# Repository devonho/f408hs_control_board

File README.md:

# Control board for Panasonic F-408HS 16" Stand Fan

## *** Warning  ***

This repository contains circuit designs for a printed circuit board that uses 240VAC as a power source, and can hence cause serious injury or death to anyone who implements the design. 

## Disclaimer

By using any of the designs here, you agree to waive the author of all liability for any personal or 3rd party injury or death, or damage to property sustained as a result of using the designs.

## License

These designs were made using a free version of [Autodesk Eagle](http://eagle.autodesk.com). Commercial use of designs is prohibited.

Furthermore: [License](./LICENSE)

## Overview

The design contained here contains both a [schematic](./eagle/F408HS_control.sch) that is inspired by the original board design, and a board [layout](./eagle/F408HS_control.brd) that has been revamped and optimized for 2-layer fabrication and debugging.

## Components and BOM

Most of the components used have been listed in the [Bill-Of-Materials](./eagle/BOM.txt) list. Some special ones that were hard to locate are connectors for the motor (CN1) and the AC input to the control board itself. These are:

* Japan Automatic Machine (JAM) SC25-10WL
* Japan Solderless Terminals (JST) ELR-03V

### Component Values

Values for transistors Q1 and Q2 were determined based on SMD markings, which may be erroneous.

Values for capacitors and zener diode were determined empirically using simulation in [LTSpice](https://www.analog.com/en/design-center/design-tools-and-calculators/ltspice-simulator.html). 

## LT SPICE Simulations

* [Power](./spice/power.asc)
* [Phase Sync](./spice/phase_sync.asc)

## Layout

The [layout](./eagle/F408HS_control.brd) was designed with 2 layer boards in mind. Without the contraints of a single layer board, J1 - J3 are no longer needed to bridge over tracks.

The 240AC tracks have also been constrained to the right side of the board, making it slightly less risky while probing the board. The AC section can also be left unpopulated, using an externally sourced Vdd and Vss via CN2 for debugging the low voltage section. 

 ## Schematic

 ### AC Phase Sync

 The output of the AC phase sync circuit is connected to P13 of the MCU. Hence it is possible that the interrupt capability of that pin is used to synchronise the TRIAC trigger with the AC phase. Modulating the TRIAC duty cycle is probably needed for the 揺らぎ "Yuragi" fluctuation function, to lower the motor RPM.

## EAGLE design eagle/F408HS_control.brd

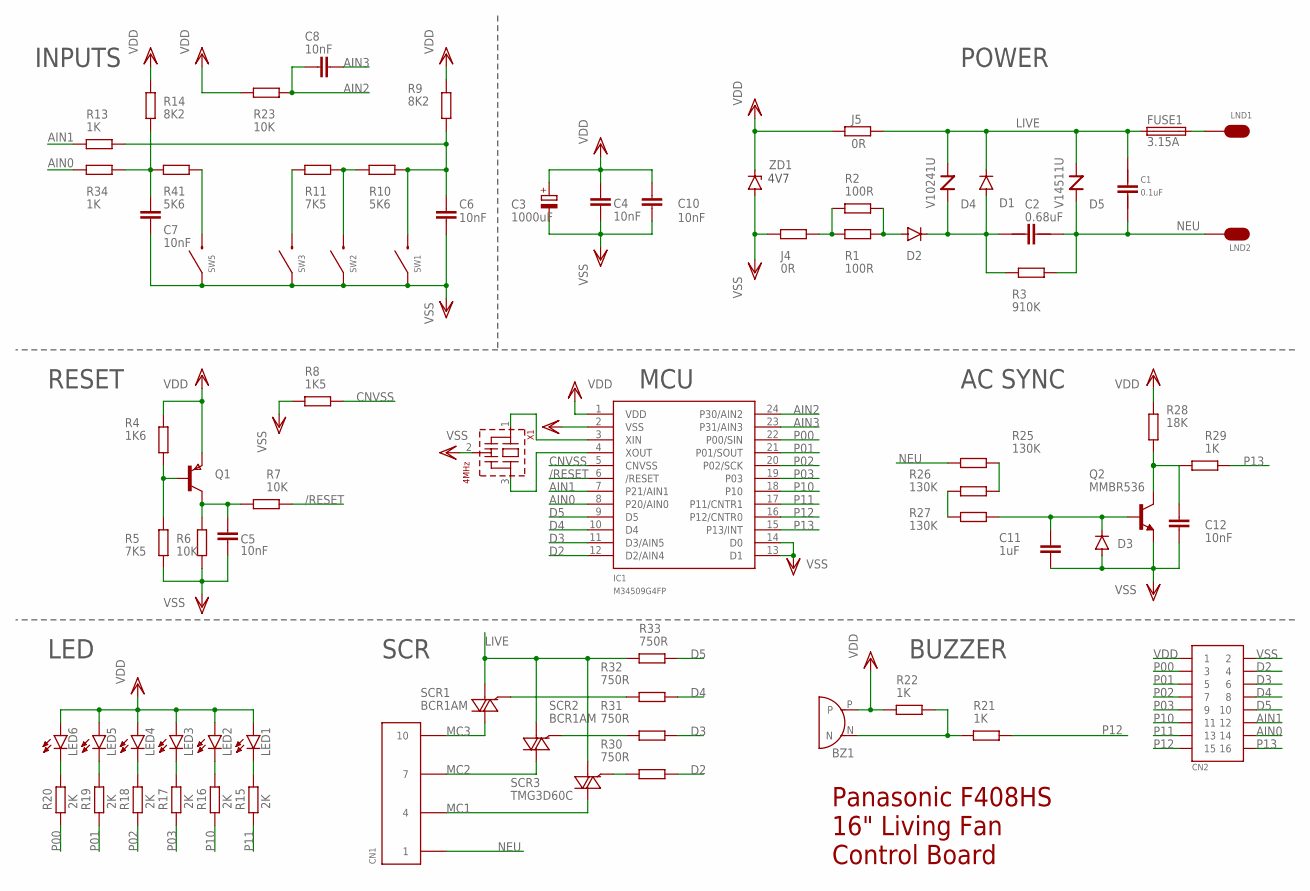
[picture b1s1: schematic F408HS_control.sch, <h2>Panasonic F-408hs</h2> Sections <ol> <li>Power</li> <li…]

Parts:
BZ1: BUZZER
C1: 0.1uF; ECQU2A104
C2: 0.68uF; ECQU2A684
C3: 1000uF; B45181B
C4, C5, C6, C7, C8, C10, C12: 10nF; C0805
C11: 1uF; C0805
CN1: SC25-10WS
CN2: HEADER16; PAK100/2500-16
D1, D2: SD103CWS-7-F; DO41-10
D3: DIODE-SOD106-W; SOD106-W
D4: V10241U; E14-S1
D5: V14511U; E14-S1
FUSE1: 3.15A; FUSE
IC1: M34509G4FP; SSOP24
J4, J5: 0R; M0805
LED1, LED2, LED3, LED4, LED5, LED6: LED_PTH_HORIZ; LED_HORIZ
LND1, LND2: LND
Q1: PNPSOT23; SOT-23
Q2: MMBR536; SOT23
R1, R2: 100R; 0204/7
R3: 910K; 0204/7
R4: 1K6; M0805
R5, R11: 7K5; M0805
R6, R7, R23: 10K; M0805
R8: 1K5; M0805
R9, R14: 8K2; M0805
R10, R41: 5K6; M0805
R13, R21, R22, R29, R34: 1K; M0805
R15, R16, R17, R18, R19, R20: 2K; M0805
R25, R26, R27: 130K; R0805
R28: 18K; M0805
R30, R31, R32, R33: 750R; M0805
SCR1, SCR2: BCR1AM; TO92
SCR3: TMG3D60C; TO220DS
SW1, SW2, SW3, SW5: EVQ11
X1: 4MHz; CSTLS_G8
ZD1: DDZ4V7ASF-7; DO35Z10

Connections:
/RESET: IC1.6 (/RESET), R7.1
AIN0: CN2.14, IC1.8 (P20/AIN0), R34.1
AIN1: CN2.12, IC1.7 (P21/AIN1), R13.1
AIN2: C8.1, IC1.24 (P30/AIN2), R23.1
AIN3: C8.2, IC1.23 (P31/AIN3)
CNVSS: IC1.5 (CNVSS), R8.1
D2: CN2.4, IC1.12 (D2/AIN4), R30.1
D3: CN2.6, IC1.11 (D3/AIN5), R31.1
D4: CN2.8, IC1.10 (D4), R32.1
D5: CN2.10, IC1.9 (D5), R33.1
LIVE: C1.P$1, D1.C, D4.P$1, D5.P$1, FUSE1.P$1 (1), J5.1, R33.2, SCR1.1 (A1), SCR2.1 (A1), SCR3.A1
MC1: CN1.P$4 (4), SCR3.A2
MC2: CN1.P$7 (7), SCR2.3 (A2)
MC3: CN1.P$10 (10), SCR1.3 (A2)
unnamed: R25.1, R26.2
unnamed: C12.2, Q2.3 (C), R28.2, R29.2
unnamed: R26.1, R27.2
unnamed: C2.P$1, D1.A, D2.C, D4.P$2, R3.1
unnamed: C6.2, R9.1, R10.2, R13.2, SW1.P$2
unnamed: C11.2, D3.C, Q2.1 (B), R27.1
unnamed: D2.A, R1.2, R2.2
unnamed: R30.2, SCR3.G
unnamed: Q1.3 (B), R4.1, R5.2
unnamed: C5.1, Q1.1 (C), R6.2, R7.2
unnamed: R10.1, R11.2, SW2.P$2
unnamed: R11.1, SW3.P$2
unnamed: R41.2, SW5.P$2
unnamed: C7.1, R14.1, R34.2, R41.1
unnamed: LED6.N (K), R20.2
unnamed: LED5.N (K), R19.2
unnamed: LED4.N (K), R18.2
unnamed: LED3.N (K), R17.2
unnamed: LED2.N (K), R16.2
unnamed: LED1.N (K), R15.2
unnamed: FUSE1.P$2 (2), LND1.P$1
unnamed: J4.1, R1.1, R2.1
unnamed: R32.2, SCR1.2 (G)
unnamed: R31.2, SCR2.2 (G)
unnamed: BZ1.N, R21.2, R22.1
unnamed: IC1.3 (XIN), X1.1
unnamed: IC1.4 (XOUT), X1.3
NEU: C1.P$2, C2.P$2, CN1.P$1 (1), D5.P$2, LND2.P$1, R3.2, R25.2
P00: CN2.3, IC1.22 (P00/SIN), R20.1
P01: CN2.5, IC1.21 (P01/SOUT), R19.1
P02: CN2.7, IC1.20 (P02/SCK), R18.1
P03: CN2.9, IC1.19 (P03), R17.1
P10: CN2.11, IC1.18 (P10), R16.1
P11: CN2.13, IC1.17 (P11/CNTR1), R15.1
P12: CN2.15, IC1.16 (P12/CNTR0), R21.1
P13: CN2.16, IC1.15 (P13/INT), R29.1
VDD: BZ1.P, C3.+, C4.1, C10.1, CN2.1, IC1.1 (VDD), J5.2, LED1.P (A), LED2.P (A), LED3.P (A), LED4.P (A), LED5.P (A), LED6.P (A), Q1.2 (E), R4.2, R9.2, R14.2, R22.2, R23.2, R28.1, ZD1.C
VSS: C3.-, C4.2, C5.2, C6.1, C7.2, C10.2, C11.1, C12.1, CN2.2, D3.A, IC1.2 (VSS), IC1.13 (D1), IC1.14 (D0), J4.2, Q2.2 (E), R5.1, R6.1, R8.2, SW1.P$1, SW2.P$1, SW3.P$1, SW5.P$1, X1.2 (VSS), ZD1.A

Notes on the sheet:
Panasonic F408HS 16" Living Fan Control Board
INPUTS
POWER
LED
MCU
RESET
AC SYNC
BUZZER
SCR
4V7

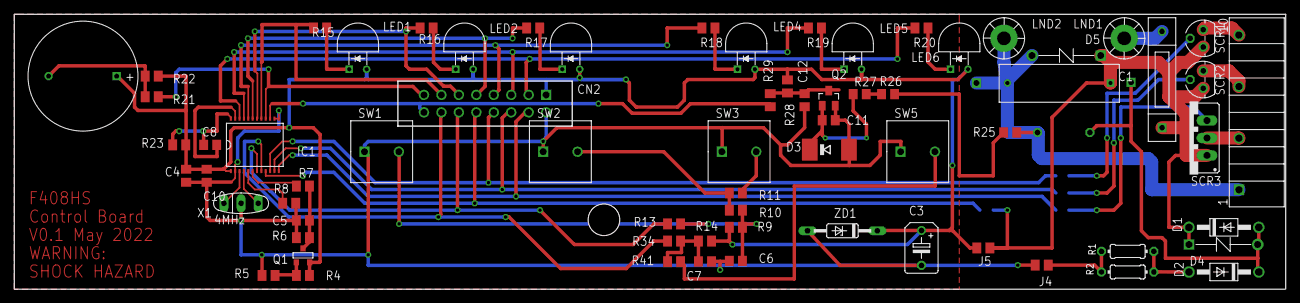
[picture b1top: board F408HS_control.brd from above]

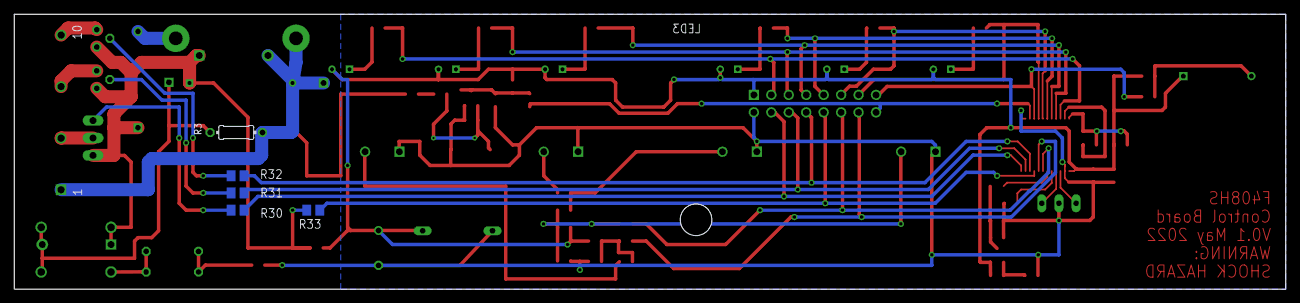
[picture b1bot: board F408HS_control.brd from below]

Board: 2 copper layers, 185.0 x 40.0 mm, 75 parts (5 on the bottom side), 52 nets.

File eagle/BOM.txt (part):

Partlist exported from C:/Users/Devon/OneDrive/projects/f408hs_control_board/eagle/F408HS_control.sch at 4/6/2022 4:26 PM

Part  Value         Device         Package        Description                                                    MF MPN         OC_FARNELL OC_NEWARK POPULARITY SPICEPREFIX
BZ1   BUZZER        BUZZER         BUZZER                                                                                                                                  
C1    0.1uF         ECQU2A104      ECQU2A104                                                                                                                               
C2    0.68uF        ECQUL2A648KL   ECQU2A684      Panasonic ECQUL Polyester Film Capacitor, 275V ac, ±10%, 680nF                                                           
C3    1000uF        CPOL-EUB45181B B45181B        POLARIZED CAPACITOR, European symbol                                                               2          C          
C4    10nF          C-EUC0805      C0805          CAPACITOR, European symbol                                                                         88         C          
C5    10nF          C-EUC0805      C0805          CAPACITOR, European symbol                                                                         88         C          
C6    10nF          C-EUC0805      C0805          CAPACITOR, European symbol                                                                         88         C          
C7    10nF          C-EUC0805      C0805          CAPACITOR, European symbol                                                                         88         C          
C8    10nF          C-EUC0805      C0805          CAPACITOR, European symbol                                                                         88         C          
C10   10nF          C-EUC0805      C0805          CAPACITOR, European symbol                                                                         88         C          
C11   1uF           C-EUC0805      C0805          CAPACITOR, European symbol                                                                         88         C          
C12   10nF          C-EUC0805      C0805          CAPACITOR, European symbol                                                                         88         C          
CN1   SC25-10WS     SC25-10WS      SC25-10WS                                                                                                                               
CN2   HEADER16      HEADER16       PAK100/2500-16                                                                                                                          
D1    SD103CWS-7-F  1N4004         DO41-10        DIODE                                                                                              82                    
D2    SD103CWS-7-F  1N4004         DO41-10        DIODE                                                                                              82                    
D3                  DIODE-SOD106-W SOD106-W       DIODE                                                                                              0                     
D4    V10241U       TVS            E14-S1         Panasonic "ZNR" Transient/Surge Absorbers"                                                                               
D5    V14511U       TVS            E14-S1         Panasonic "ZNR" Transient/Surge Absorbers"                                                                               
FUSE1 3.15A         FUSE           FUSE                                                                                                                                    
IC1   M34509G4FP    M34509G4FP     SSOP24                                                                                                                                  
J4    0R            R-EU_M0805     M0805          RESISTOR, European symbol                                                                          45         R          
J5    0R            R-EU_M0805     M0805          RESISTOR, European symbol                                                                          45         R          
LED1  LED_PTH_HORIZ LED_PTH_HORIZ  LED_HORIZ                                                                                                                               
LED2  LED_PTH_HORIZ LED_PTH_HORIZ  LED_HORIZ                                                                                                                               
LED3  LED_PTH_HORIZ LED_PTH_HORIZ  LED_HORIZ                                                                                                                               
LED4  LED_PTH_HORIZ LED_PTH_HORIZ  LED_HORIZ                                                                                                                               
LED5  LED_PTH_HORIZ LED_PTH_HORIZ  LED_HORIZ                                                                                                                               
LED6  LED_PTH_HORIZ LED_PTH_HORIZ  LED_HORIZ                                                                                                                               
LND1  LND           LND            LND                                                                                                                                     
LND2  LND           LND            LND                                                                                                                                     
Q1                  PNPSOT23       SOT-23         PNP TRANSISTOR                                                    DSS20200L-7 unknown    25R4554   0                     
Q2    MMBR536       MMBR536        SOT23                                                                                                                                   
R1    100R          R-EU_0204/7    0204/7         RESISTOR, European symbol                                                                          79         R          
R2    100R          R-EU_0204/7    0204/7         RESISTOR, European symbol                                                                          79         R          
R3    910K          R-EU_0204/7    0204/7         RESISTOR, European symbol                                                                          79         R          
R4    1K6           R-EU_M0805     M0805          RESISTOR, European symbol                                                                          45         R          
R5    7K5           R-EU_M0805     M0805          RESISTOR, European symbol                                                                          45         R          
R6    10K           R-EU_M0805     M0805          RESISTOR, European symbol                                                                          45         R          
R7    10K           R-EU_M0805     M0805          RESISTOR, European symbol                                                                          45         R          
R8    1K5           R-EU_M0805     M0805          RESISTOR, European symbol                                                                          45         R          
R9    8K2           R-EU_M0805     M0805          RESISTOR, European symbol                                                                          45         R          
R10   5K6           R-EU_M0805     M0805          RESISTOR, European symbol                                                                          45         R          
R11   7K5           R-EU_M0805     M0805          RESISTOR, European symbol                                                                          45         R          
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
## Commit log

2022-06-04 Initial checkin
2022-06-04 added board image
2022-06-04 README.md update
